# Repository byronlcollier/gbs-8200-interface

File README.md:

# gbs-8200-interface
KiCad files for a custom interface to the GBS-8200 range of upscalers.

This project is public domain - I stand on the shoulders of others, so I won't take credit for their work.

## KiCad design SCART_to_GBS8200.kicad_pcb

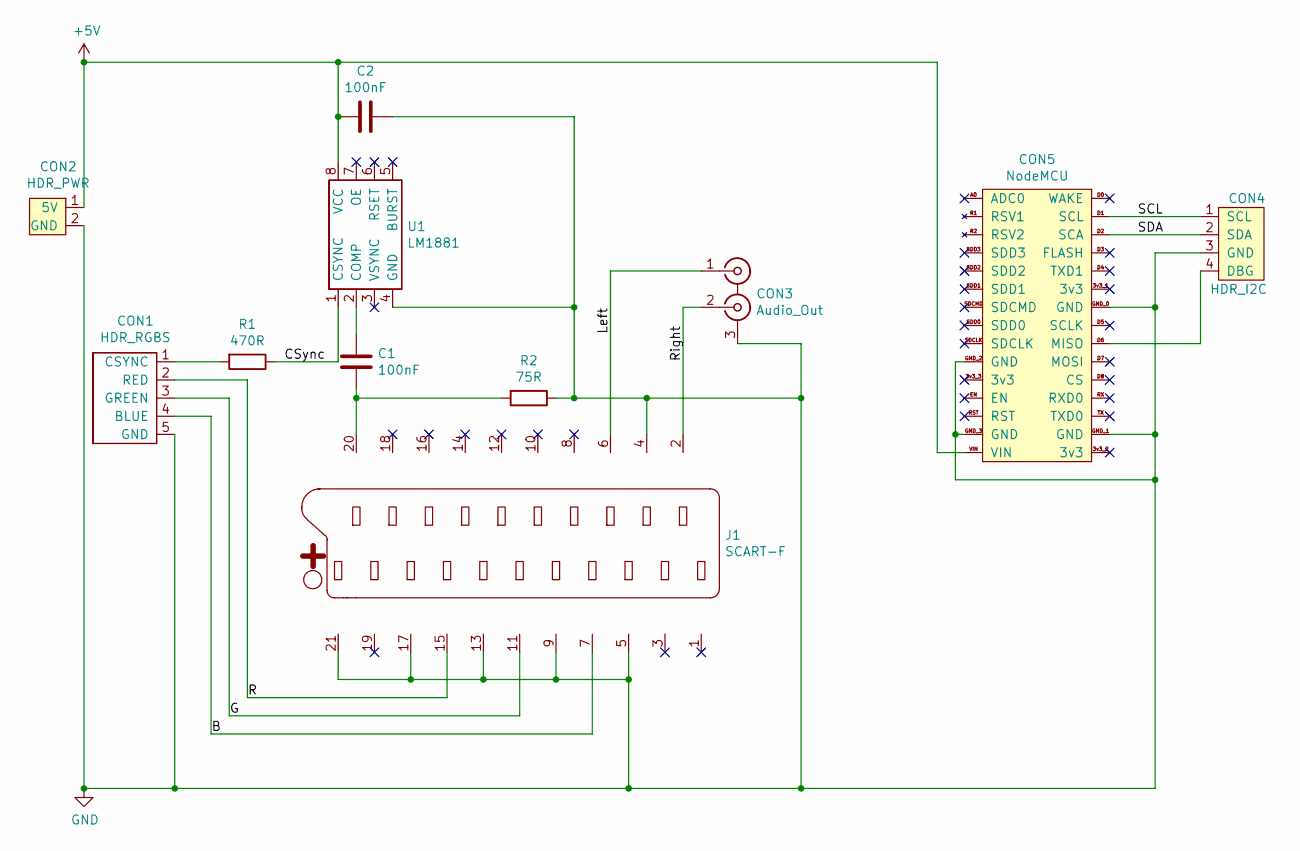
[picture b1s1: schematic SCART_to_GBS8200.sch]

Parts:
C1, C2: 100nF; C_Disc_D5.0mm_W2.5mm_P5.00mm
CON1: HDR_RGBS; PinHeader_1x05_P2.54mm_Vertical
CON2: HDR_PWR; PinHeader_1x02_P2.54mm_Vertical
CON3: Audio_Out; PinHeader_1x03_P2.54mm_Vertical
CON4: HDR_I2C; PinHeader_1x04_P2.54mm_Vertical
CON5: NodeMCU; NodeMCU_r2
J1: SCART-F; SCART_PCBMount
R1: 470R; R_Axial_DIN0207_L6.3mm_D2.5mm_P10.16mm_Horizontal
R2: 75R; R_Axial_DIN0207_L6.3mm_D2.5mm_P10.16mm_Horizontal
U1: LM1881; DIP-8_W7.62mm

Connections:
+5V: C2.2, CON2.1 (5V), CON5.VIN, U1.8 (VCC)
/B: CON1.4 (BLUE), J1.7 (B)
/CSync: R1.1, U1.1 (CSYNC)
/G: CON1.3 (GREEN), J1.11 (G)
/Left: CON3.1 (IN1), J1.6 (AIL)
/R: CON1.2 (RED), J1.15 (R)
/Right: CON3.2 (IN2), J1.2 (AIR)
/SCL: CON4.1 (SCL), CON5.D1 (SCL)
/SDA: CON4.2 (SDA), CON5.D2 (SCA)
GND: C2.1, CON1.5 (GND), CON2.2 (GND), CON3.3 (EXT), CON4.3 (GND), CON5.GND_0 (GND), CON5.GND_1 (GND), CON5.GND_2 (GND), CON5.GND_3 (GND), J1.4 (AGND), J1.5 (BGND), J1.9 (GGND), J1.13 (RGND), J1.17 (VGND), J1.21 (GND), R2.1, U1.4 (GND)
unnamed: C1.1, U1.2 (COMP)
unnamed: C1.2, J1.20 (CVIN), R2.2
unnamed: CON1.1 (CSYNC), R1.2
unnamed: CON4.4 (DBG), CON5.D6 (MISO)

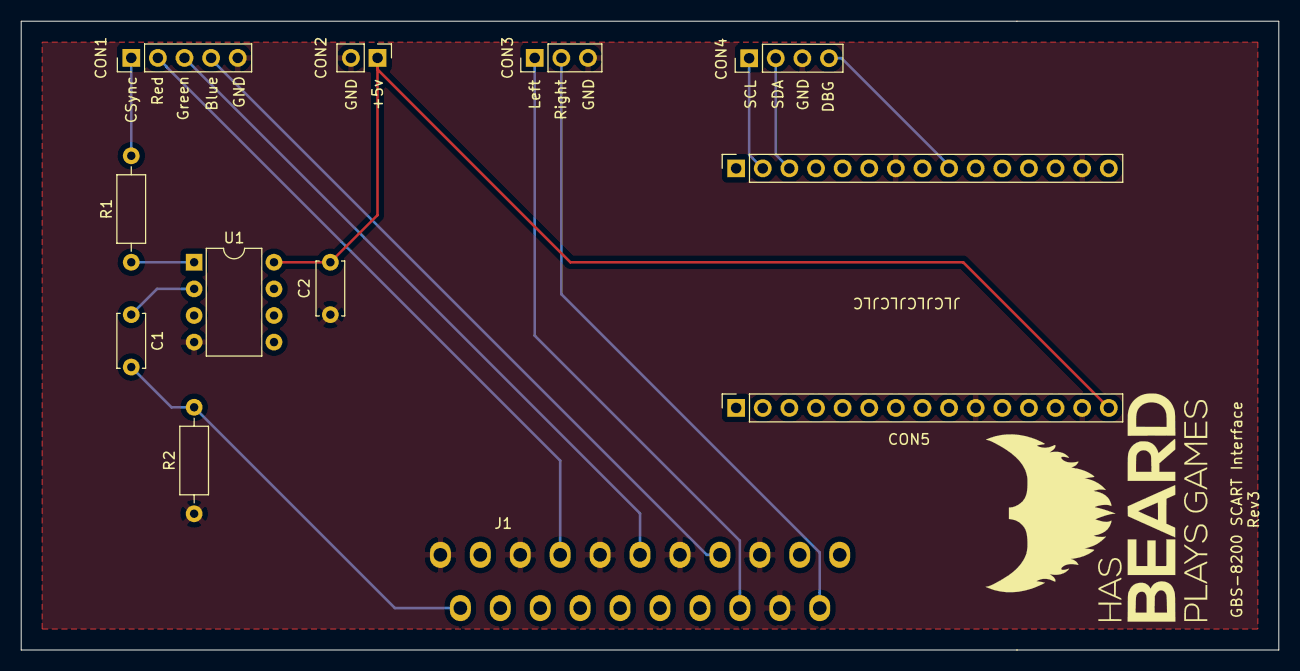
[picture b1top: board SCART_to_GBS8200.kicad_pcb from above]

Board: 2 copper layers, 120.0 x 60.0 mm, 11 parts (0 on the bottom side), 14 nets.

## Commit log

2021-01-12 Committing all files from local machine
